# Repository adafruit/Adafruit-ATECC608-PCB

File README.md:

## Adafruit Adafruit ATECC608 Breakout Board - STEMMA QT / Qwiic PCB

<a href="http://www.adafruit.com/products/4314"><br/>
Click here to purchase one from the Adafruit shop</a>

PCB files for the Adafruit Adafruit ATECC608 Breakout Board - STEMMA QT / Qwiic. 

Format is EagleCAD schematic and board layout
* https://www.adafruit.com/product/4314

### Description

You've got secrets, and you want to keep them safe? Most microcontrollers are not designed to protect against snoopers, but a crypto-authentication chip can be used to lock away private keys securely. Once the private key is saved inside, it can't be read out, all you can do is send it challenge-response queries. That means that even if someone gets hold of your hardware and can read back the firmware, they wont be able to extract the secret!

The ATECC608 is the latest crypto-auth chip from Microchip, and it uses I2C to send/receive commands. Once you 'lock' the chip with your details, you can use it for ECDH and AES-128 encrypt/decrypt/signing. There's also hardware support for random number generation, and SHA-256/HMAC hash functions to  greatly speed up a slower micro's cryptography commands.

### License

Adafruit invests time and resources providing this open source design, please support Adafruit and open-source hardware by purchasing products from [Adafruit](https://www.adafruit.com)!

Designed by Limor Fried/Ladyada for Adafruit Industries.

Creative Commons Attribution/Share-Alike, all text above must be included in any redistribution. 
See license.txt for additional details.

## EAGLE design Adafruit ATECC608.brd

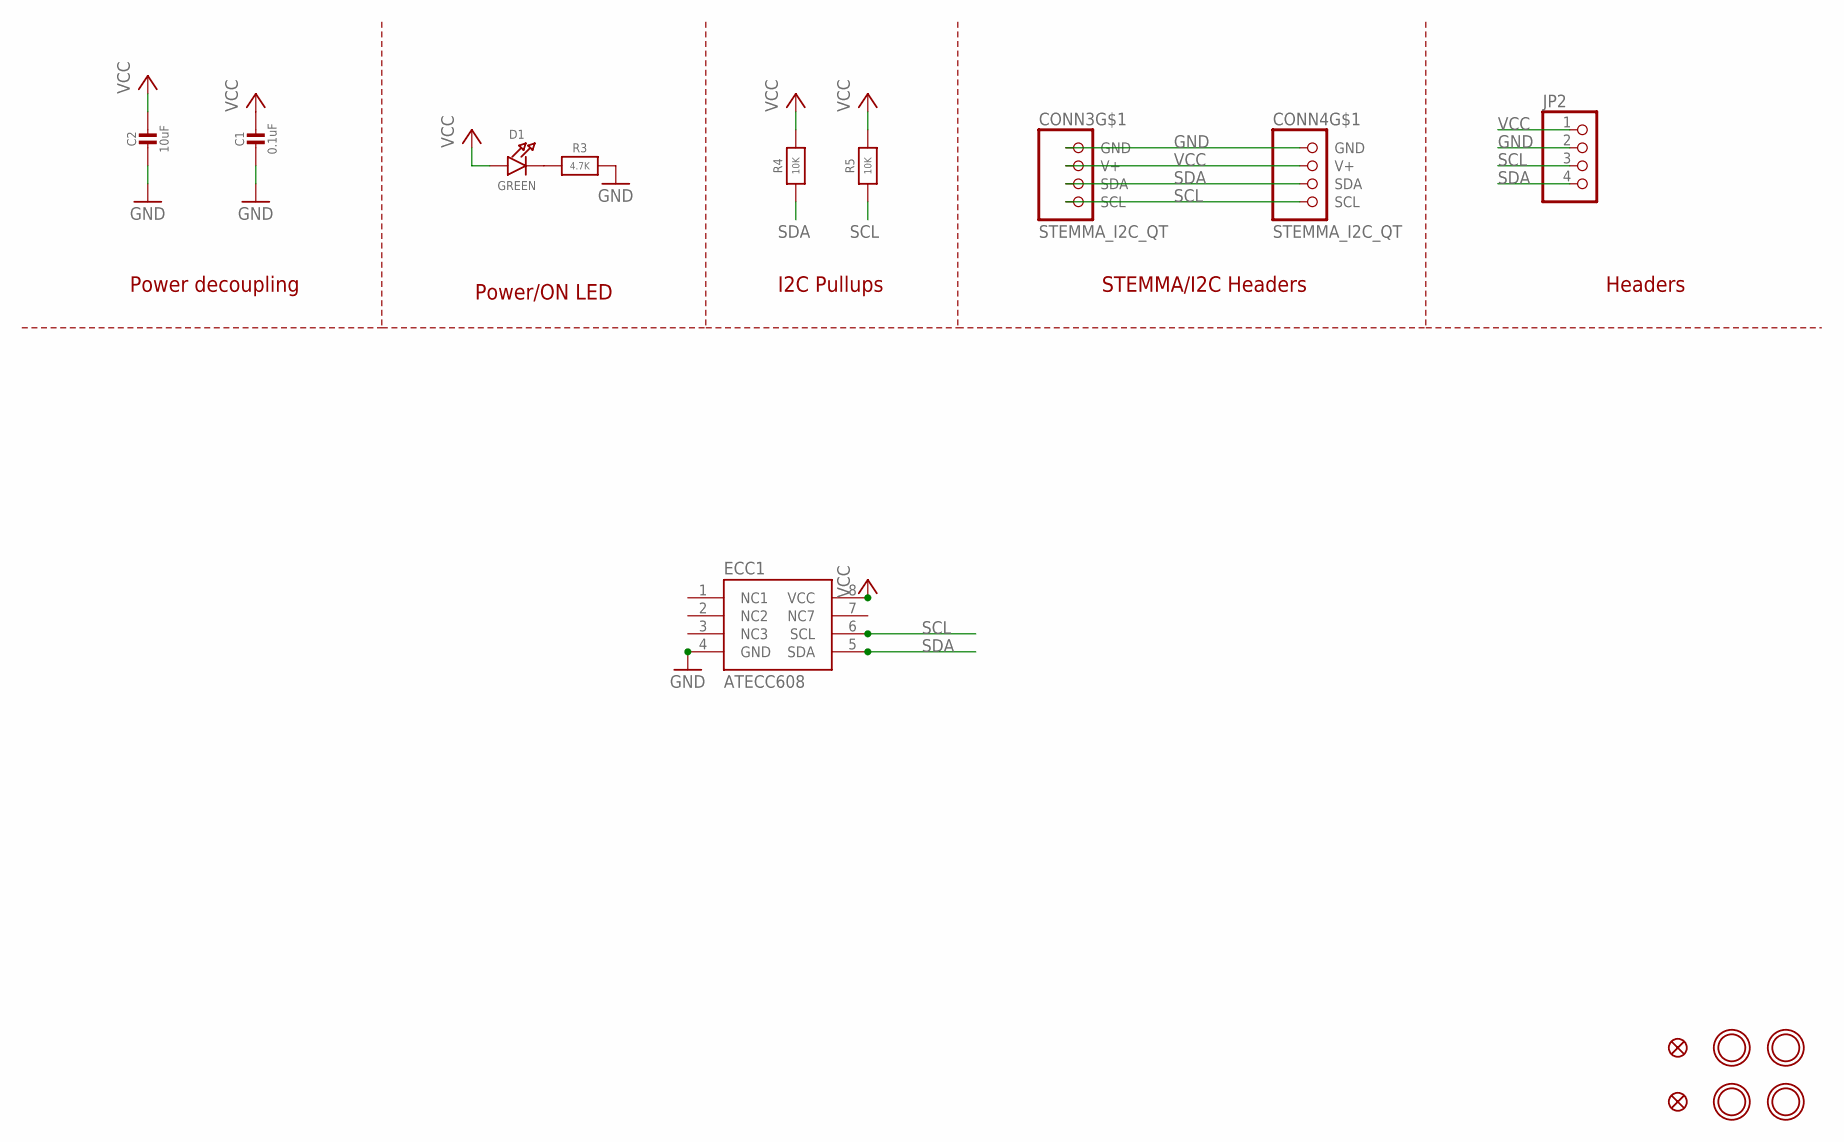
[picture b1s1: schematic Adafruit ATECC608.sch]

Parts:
C1: 0.1uF; 0603-NO
C2: 10uF; 0805-NO
CONN3, CONN4: STEMMA_I2C_QT; JST_SH4
D1: GREEN; CHIPLED_0603_NOOUTLINE
ECC1: ATECC608; SOIC8
FID3, FID4: FIDUCIAL_1MM
JP2: HEADER-1X4ROUND; 1X04_ROUND
R3: 4.7K; 0603-NO
R4, R5: 10K; 0603-NO
U$11, U$12, U$14, U$15: MOUNTINGHOLE2.5; MOUNTINGHOLE_2.5_PLATED

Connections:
GND: C1.2, C2.2, CONN3.1 (GND), CONN4.1 (GND), ECC1.4 (GND), JP2.2, R3.2
unnamed: D1.C, R3.1
SCL: CONN3.4 (SCL), CONN4.4 (SCL), ECC1.6 (SCL), JP2.3, R5.1
SDA: CONN3.3 (SDA), CONN4.3 (SDA), ECC1.5 (SDA), JP2.4, R4.1
VCC: C1.1, C2.1, CONN3.2 (V+), CONN4.2 (V+), D1.A, ECC1.8 (VCC), JP2.1, R4.2, R5.2

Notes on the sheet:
Power/ON LED
Power decoupling
I2C Pullups
STEMMA/I2C Headers
Headers

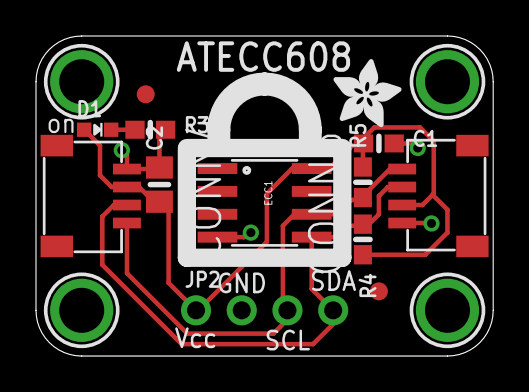
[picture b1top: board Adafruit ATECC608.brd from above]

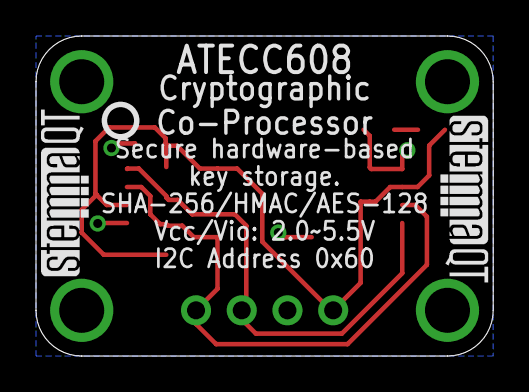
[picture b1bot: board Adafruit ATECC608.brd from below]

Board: 2 copper layers, 25.4 x 17.8 mm, 20 parts (3 on the bottom side), 5 nets.

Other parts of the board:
U$17: ADAFRUIT_3.5MM
U$18: PCBFEAT-REV-040
U$19, U$20: STEMMAQT

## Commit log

2019-08-30 Adding files.

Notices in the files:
parts and their libraries:
microbuilder: This work is placed in the public domain, and may be freely used for commercial and non-commercial work with the following conditions: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
